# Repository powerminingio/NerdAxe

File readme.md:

# The Nerdaxe
NerdAxe is a fork from bitaxe with fullcolor display graphics. NerdAxe is indented to be an upgrade board for these who have a NerdMiner and would like to have more powerful mining features without losing the NerdMiner essence. That's why NerdAxe is currently controlled by the common board used on Nerdminer project called TTGO-TDisplayS3.

Currently exists two variants sepparated in two branches:
- **Nerdaxe Gamma**: 1,2Th with a single chip BM1370. [Nerdaxe Gamma](https://github.com/BitMaker-hub/NerdAxe/tree/gamma-1%2C2Ths)
- **Nerdaxe Ultra**: 0,5Th with a single chip BM1366. [Nerdaxe Ultra](https://github.com/BitMaker-hub/NerdAxe/tree/ultra-500Ghs)

The following fork could not be possible without the previous work of @skot, @ben & bitaxe devs. [Check bitaxe project](https://bitaxe.org)

Upgrade your NerdMiner experience throught this addon board and start playing with ASICs

## Goals
- **Plug&Play**: your NerdMiner board and convert it into a NerdAxe.
- **Standalone**: can mine directly to your pool over WiFi. No External computer needed.
- **Embedded**: low cost, low maintenance, high availability, high reliability, low power.
- **ASIC**: working with most efficient ASIC chips from Bitmain - BM1370.
- **Versatile**: solo/pool mining, autotune power/heat/efficiency.
- **Open Source**: All design files are provided.

## Features
- **TTGO-TDisplay** ESP32s3 wifi microcontroller display board
- **Multiple Screens** to allow you see all the miner stats 
- **TI TPS546D** buck regulator steps down the 5V input to power the BM1370
- **Microchip EMC2101** PWM controls the fan and monitors tach output. Measuring internal die temp isn't working.

## Additional Features added by Powermining
- **Two fan connectors** - no need for splitter cable if you use secondary fan.
- **Threaded heatsink mounting holes** PCB with M3 threads for firm heatsink mounting
- **OG matching heatsink bolt pattern** no headache with non fitting standard bolt patterns! We keep the Nerdaxe standard 41.49x41.35

## Software & Firmware
Nerdaxe firmware was forked from original ESP-Miner version and adapted to use TTGO board and LVGL as graphic interface lib. 
Check it here -> [ESP-Miner Nerdaxe version](https://github.com/BitMaker-hub/ESP-Miner-NerdAxe)

**Today** Nerdaxe is using the latest evolution of this firmware modified by @pmaxuw (creator of the NerdQaxe) and used for other multiple boards
Current firmware -> [ESP-Miner Nerd\*axe version](https://github.com/shufps/ESP-Miner-NerdQAxePlus)

Flash the latest Nerdaxe firmware here: 
- Go to flasher online tool: https://flasher.bitronics.store/ (recommend via Google Chrome incognito mode)
- Nerd\*axe flasher online tool: https://shufps.github.io/nerdqaxe-web-flasher/  

## The DIY area

### Asic BM1370
- The BM1370 is a undocumented SHA256 mining ASIC from Bitmain. It's mostly used in the Antminer S21pro/S21+
- Bitmain claims the BM1370 has 0.021J/GH efficiency
- The BM1370 is available (new) for around $60 each in small quantities.
- The BM1370 has a different footprint and pinout from the MB1366, BM1368 in previous bitaxe.

### Other components & build troubleshooting
- BM1370 from NBTC on AliExpress
- [40x40mm heatsink and 5V fan](https://www.aliexpress.com/item/2251832861666365.html) from a random AliExpress seller. At least half of these arrived broken in some way. But they are cheap and the working ones do keep the BM1387's nice and cool when used with some thermal compound.
    - Swap this fan with the [Noctua NF-A4x10](https://noctua.at/en/products/fan/nf-a4x10-pwm) 5V 4-Pin fan for a much more pleasant experience.
- Board is designed with [KiCad 8](https://www.kicad.org) design files
- All of the parts on the board are listed in the KiCad BOM
- Check out [building.md](building.md) for PCB ordering tips
- Check out [assembly.md](assembly.md) for assembly tips

### Power Supply Requirements
- 5VDC Power supply 5A minimum. Should be capable of over 25W

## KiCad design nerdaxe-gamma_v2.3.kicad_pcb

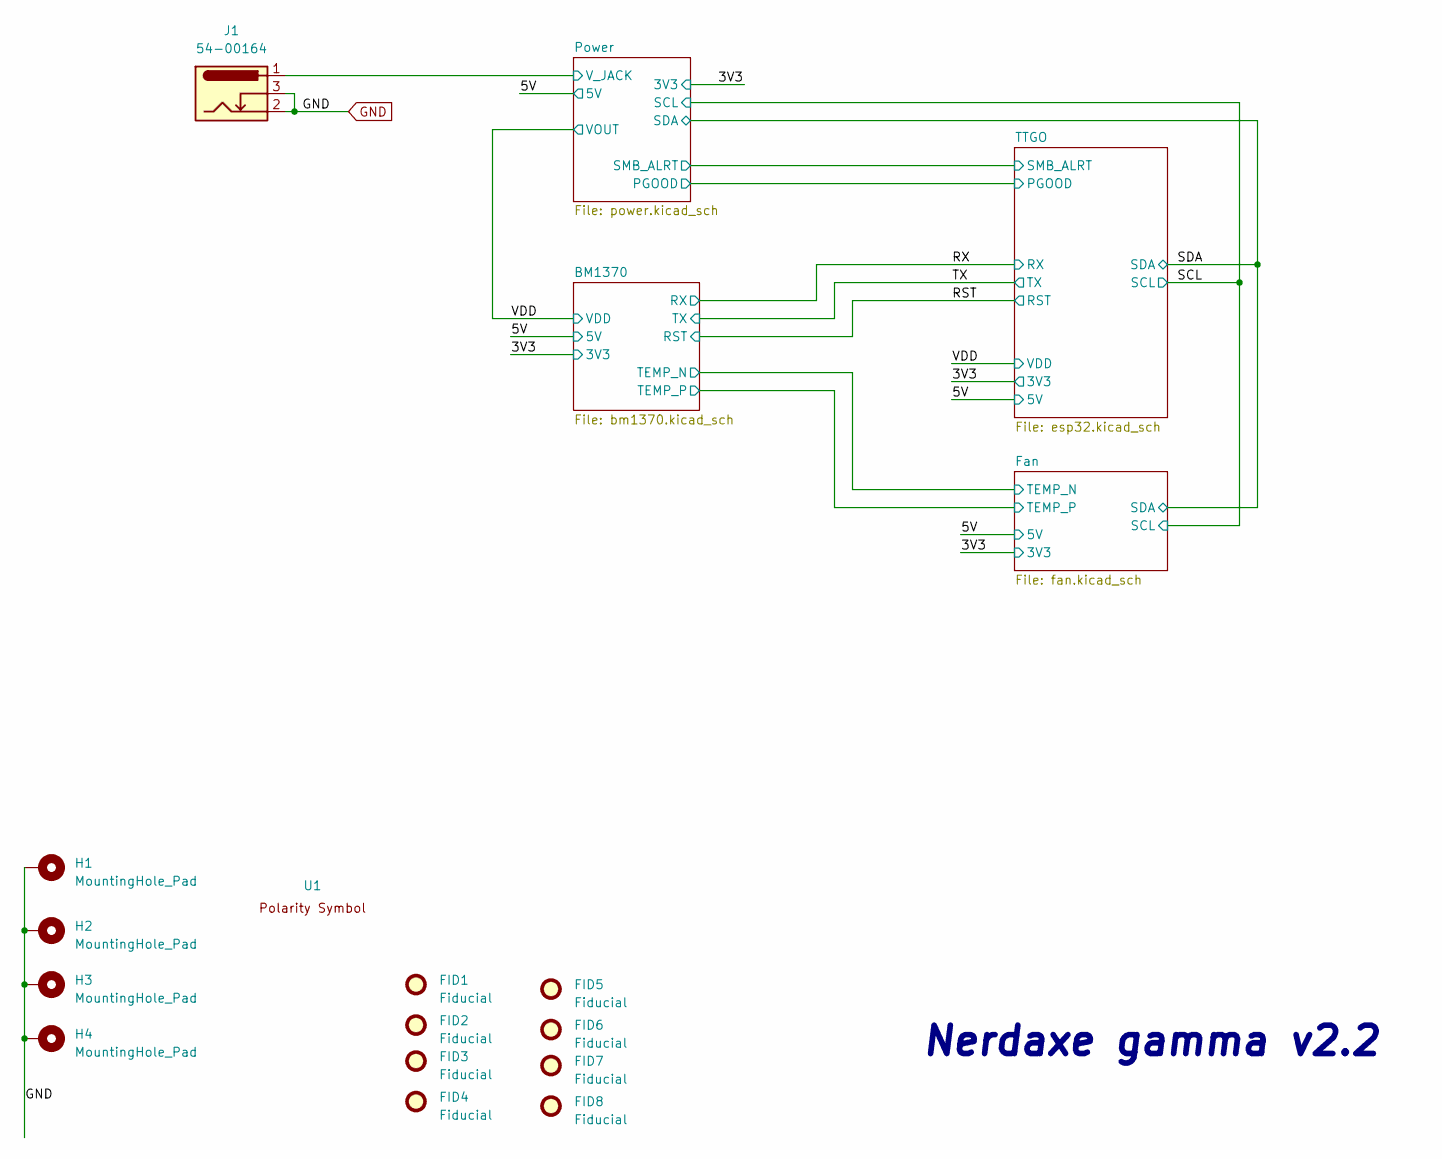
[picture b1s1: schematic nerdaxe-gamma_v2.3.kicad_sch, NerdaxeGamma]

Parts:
FID1, FID2, FID3, FID4, FID5, FID6, FID7, FID8: Fiducial; Fiducial_1mm_Mask2mm
H1, H2, H3, H4: MountingHole_Pad; MountingHole_3mm_Pad_Via
J1: 54-00164; TENSILITY_54-00164; PARTNO 54-00164; LCSC C431534
U1: polarity

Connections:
/Power/V_JACK: J1.1; also elsewhere on the board
GND: H1.1, H2.1, H3.1, H4.1, J1.2, J1.3; also elsewhere on the board

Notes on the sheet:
Nerdaxe gamma v2.2

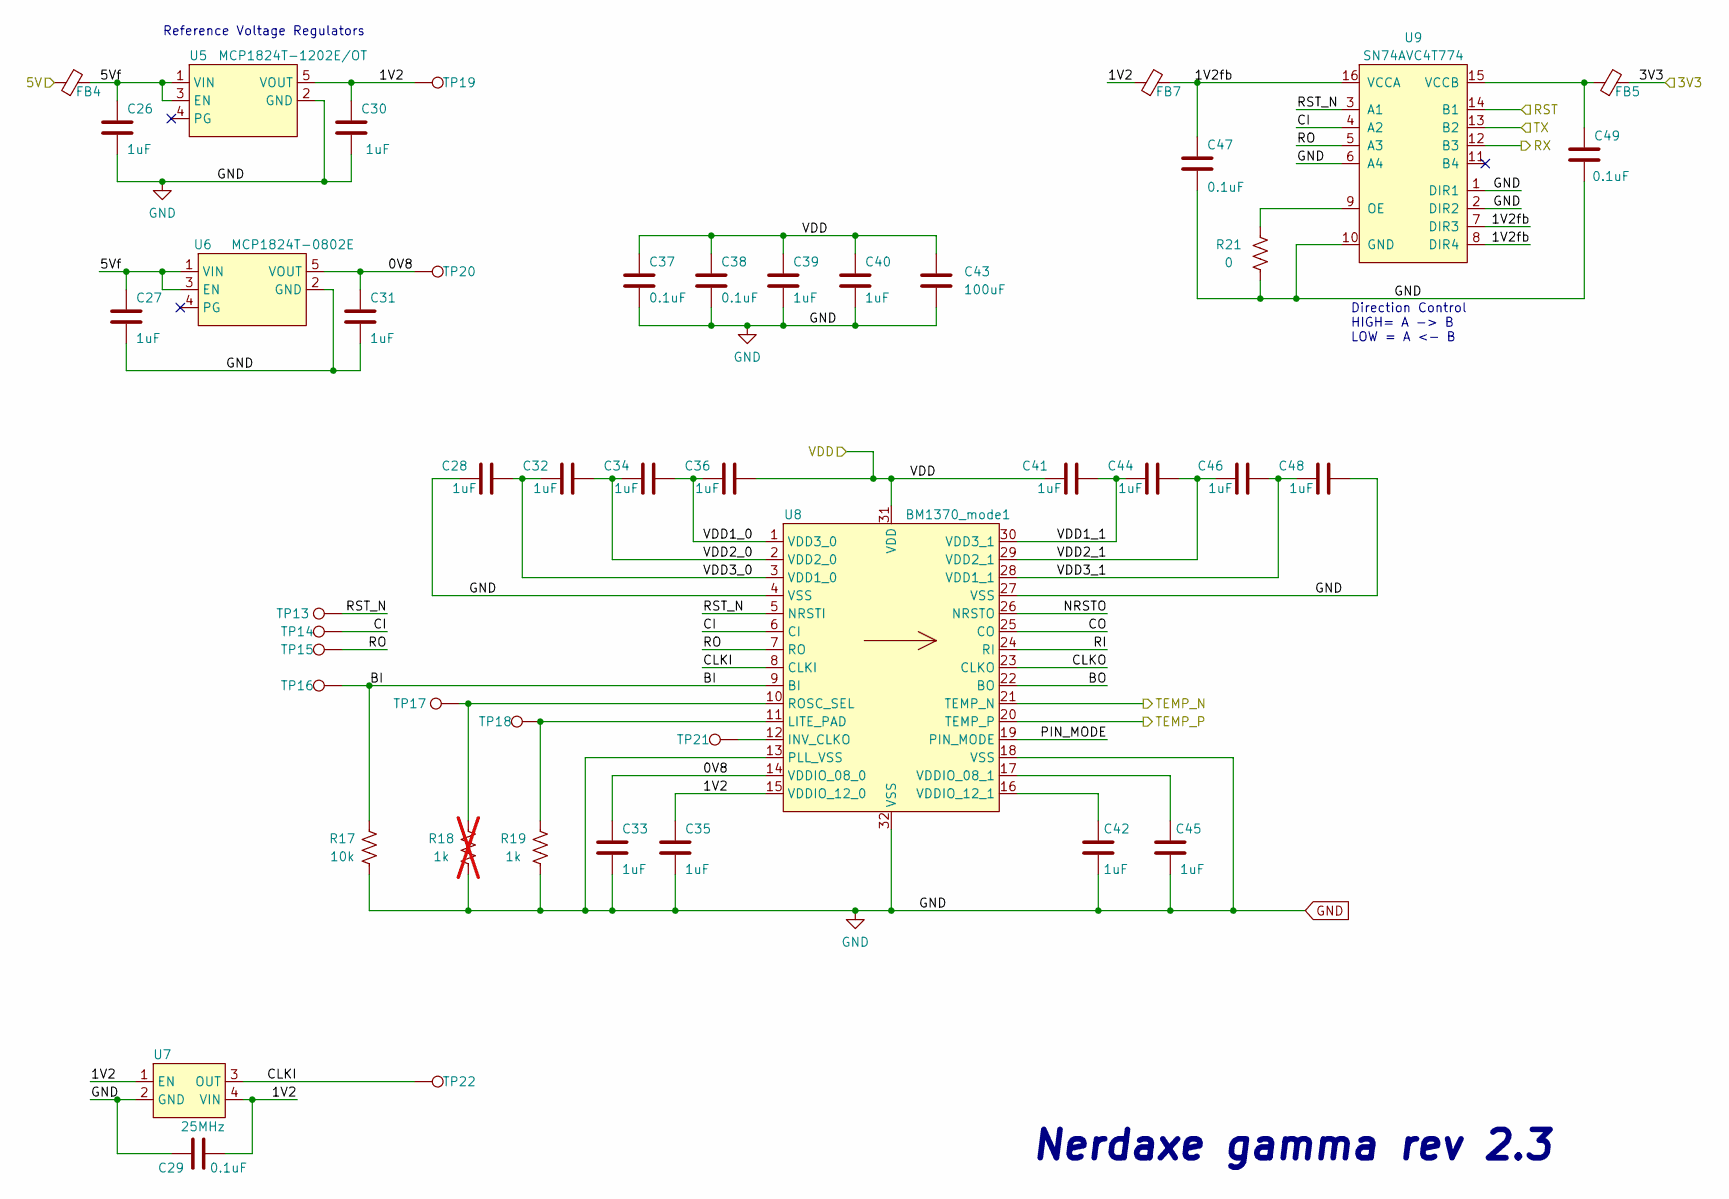
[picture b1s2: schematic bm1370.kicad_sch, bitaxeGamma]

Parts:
C26, C27, C28, C30, C31, C32, C33, C34, C35, C36, C39, C40, C41, C42, C44, C45, C46, C48: 1uF; C_0402_1005Metric; PARTNO EMK105BJ105MV-F
C29, C37, C38, C47, C49: 0.1uF; C_0402_1005Metric; PARTNO CL05A104KO5NNNC
C43: 100uF; C_1206_3216Metric; PARTNO CL31A107MQHNNNE
FB4, FB5, FB7: BLM21PG221SN1D; R_0805_2012Metric
R17: 10k; R_0402_1005Metric; PARTNO RC0402JR-0710KL
R18: 1k; R_0402_1005Metric; PARTNO RC0402FR-071KL; not fitted
R19: 1k; R_0402_1005Metric; PARTNO RC0402FR-071KL
R21: 0; R_0402_1005Metric; PARTNO RC0402FR-0720KL
TP13, TP14, TP15, TP16, TP17, TP18, TP19, TP20, TP21, TP22: TestPoint; TestPoint_Pad_D1.5mm
U5: MCP1824T-1202E/OT; SOT-23-5; PARTNO MCP1824T-1202E/OT
U6: MCP1824T-0802E; SOT-23-5; PARTNO MCP1824T-0802E/OT
U7: 25MHz; SMD3225-4P; PARTNO SX3M25.000E20F30THN; LCSC C5137262
U8: BM1370_mode1; BM1370
U9: SN74AVC4T774; TSSOP-16_4.4x5mm_P0.65mm; PARTNO SN74AVC4T774PWR

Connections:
/3V3: FB5.2; also elsewhere on the board
/5V: FB4.1; also elsewhere on the board
/BM1370/0V8: C31.1, C33.1, TP20.1, U6.5 (VOUT), U8.14 (VDDIO_08_0)
/BM1370/1V2: C29.2, C30.1, C35.1, FB7.1, TP19.1, U5.5 (VOUT), U7.1 (EN), U7.4 (VIN), U8.15 (VDDIO_12_0)
/BM1370/1V2fb: C47.1, FB7.2, U9.7 (DIR3), U9.8 (DIR4), U9.16 (VCCA)
/BM1370/5Vf: C26.1, C27.1, FB4.2, U5.1 (VIN), U5.3 (EN), U6.1 (VIN), U6.3 (EN)
/BM1370/BI: R17.2, TP16.1, U8.9 (BI)
/BM1370/BO: U8.22 (BO)
/BM1370/CI: TP14.1, U8.6 (CI), U9.4 (A2)
/BM1370/CLKI: TP22.1, U7.3 (OUT), U8.8 (CLKI)
/BM1370/CLKO: U8.23 (CLKO)
/BM1370/CO: U8.25 (CO)
/BM1370/NRSTO: U8.26 (NRSTO)
/BM1370/PIN_MODE: U8.19 (PIN_MODE)
/BM1370/RI: U8.24 (RI)
/BM1370/RO: TP15.1, U8.7 (RO), U9.5 (A3)
/BM1370/RST_N: TP13.1, U8.5 (NRSTI), U9.3 (A1)
/BM1370/VDD1_0: C34.2, C36.1, U8.1 (VDD3_0)
/BM1370/VDD1_1: C41.2, C44.1, U8.30 (VDD3_1)
/BM1370/VDD2_0: C32.2, C34.1, U8.2 (VDD2_0)
/BM1370/VDD2_1: C44.2, C46.1, U8.29 (VDD2_1)
/BM1370/VDD3_0: C28.2, C32.1, U8.3 (VDD1_0)
/BM1370/VDD3_1: C46.2, C48.1, U8.28 (VDD1_1)
/Fan/TEMP_N: U8.21 (TEMP_N); also elsewhere on the board
/Fan/TEMP_P: U8.20 (TEMP_P); also elsewhere on the board
/RST: U9.14 (B1); also elsewhere on the board
/RX: U9.12 (B3); also elsewhere on the board
/TX: U9.13 (B2); also elsewhere on the board
/VDD: C36.2, C37.1, C38.1, C39.1, C40.1, C41.1, C43.1, U8.31 (VDD); also elsewhere on the board
GND: C26.2, C27.2, C28.1, C29.1, C30.2, C31.2, C33.2, C35.2, C37.2, C38.2, C39.2, C40.2, C42.2, C43.2, C45.2, C47.2, C48.2, C49.2, R17.1, R18.1, R19.1, R21.1, U5.2 (GND), U6.2 (GND), U7.2 (GND), U8.4 (VSS), U8.13 (PLL_VSS), U8.18 (VSS), U8.27 (VSS), U8.32 (VSS), U9.1 (DIR1), U9.2 (DIR2), U9.6 (A4), U9.10 (GND); also elsewhere on the board
unnamed: TP21.1, U8.12 (INV_CLKO)
unnamed: R19.2, TP18.1, U8.11 (LITE_PAD)
unnamed: R18.2, TP17.1, U8.10 (ROSC_SEL)
unnamed: C45.1, U8.17 (VDDIO_08_1)
unnamed: C42.1, U8.16 (VDDIO_12_1)
unnamed: R21.2, U9.9 (OE)
unnamed: C49.1, FB5.1, U9.15 (VCCB)

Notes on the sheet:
Reference Voltage Regulators
Direction Control HIGH= A -> B LOW = A <- B
Nerdaxe gamma rev 2.3

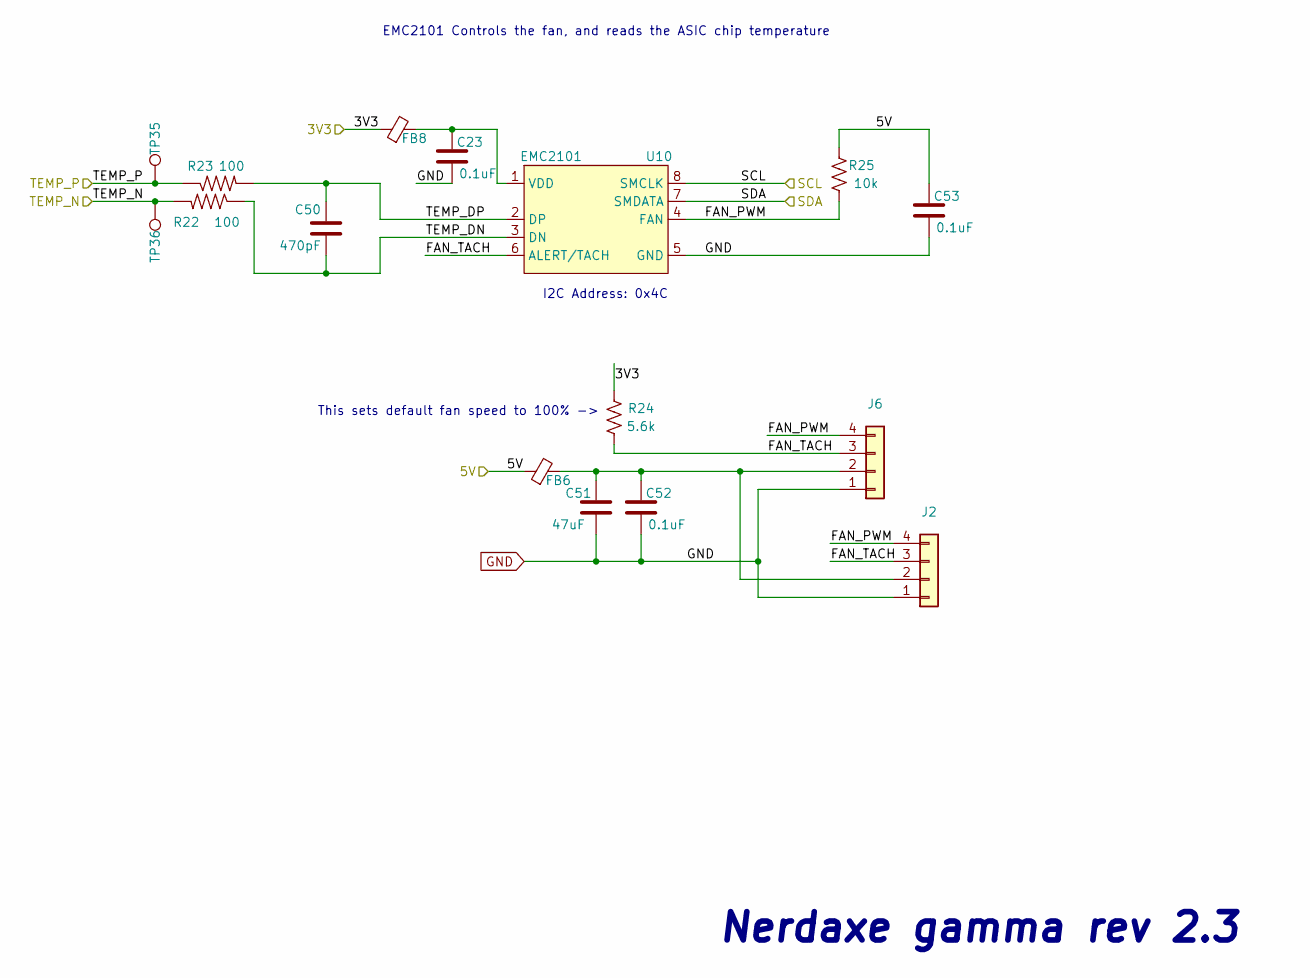
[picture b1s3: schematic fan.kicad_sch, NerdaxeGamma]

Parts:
C23, C52, C53: 0.1uF; C_0402_1005Metric; PARTNO CL05A104KO5NNNC
C50: 470pF; C_0402_1005Metric; PARTNO CL05B471KB5NNNC
C51: 47uF; C_1210_3225Metric; PARTNO CL32A476KOJNNNE
FB6, FB8: BLM21PG221SN1D; R_0805_2012Metric
J2, J6: Conn_01x04; 470531000; PARTNO 0470531000
R22, R23: 100; R_0402_1005Metric; PARTNO RC0402FR-07100RL
R24: 5.6k; R_0402_1005Metric; PARTNO RC0402FR-135K6L
R25: 10k; R_0402_1005Metric; PARTNO RC0402JR-0710KL
TP35, TP36: TestPoint; TestPoint_Pad_D1.5mm
U10: EMC2101; TSSOP-8_3x3mm_P0.65mm; PARTNO EMC2101-R-ACZL-TR

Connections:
/3V3: FB8.1, R24.2; also elsewhere on the board
/5V: C53.1, FB6.1, R25.2; also elsewhere on the board
/Fan/FAN_PWM: J2.4, J6.4, R25.1, U10.4 (FAN)
/Fan/FAN_TACH: J2.3, J6.3, R24.1, U10.6 (ALERT/TACH)
/Fan/TEMP_DN: C50.2, R22.1, U10.3 (DN)
/Fan/TEMP_DP: C50.1, R23.2, U10.2 (DP)
/Fan/TEMP_N: R22.2, TP36.1; also elsewhere on the board
/Fan/TEMP_P: R23.1, TP35.1; also elsewhere on the board
/SCL: U10.8 (SMCLK); also elsewhere on the board
/SDA: U10.7 (SMDATA); also elsewhere on the board
GND: C23.2, C51.2, C52.2, C53.2, J2.1, J6.1, U10.5 (GND); also elsewhere on the board
unnamed: C51.1, C52.1, FB6.2, J2.2, J6.2
unnamed: C23.1, FB8.2, U10.1 (VDD)

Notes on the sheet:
Nerdaxe gamma rev 2.3
EMC2101 Controls the fan, and reads the ASIC chip temperature
This sets default fan speed to 100% ->
I2C Address: 0x4C

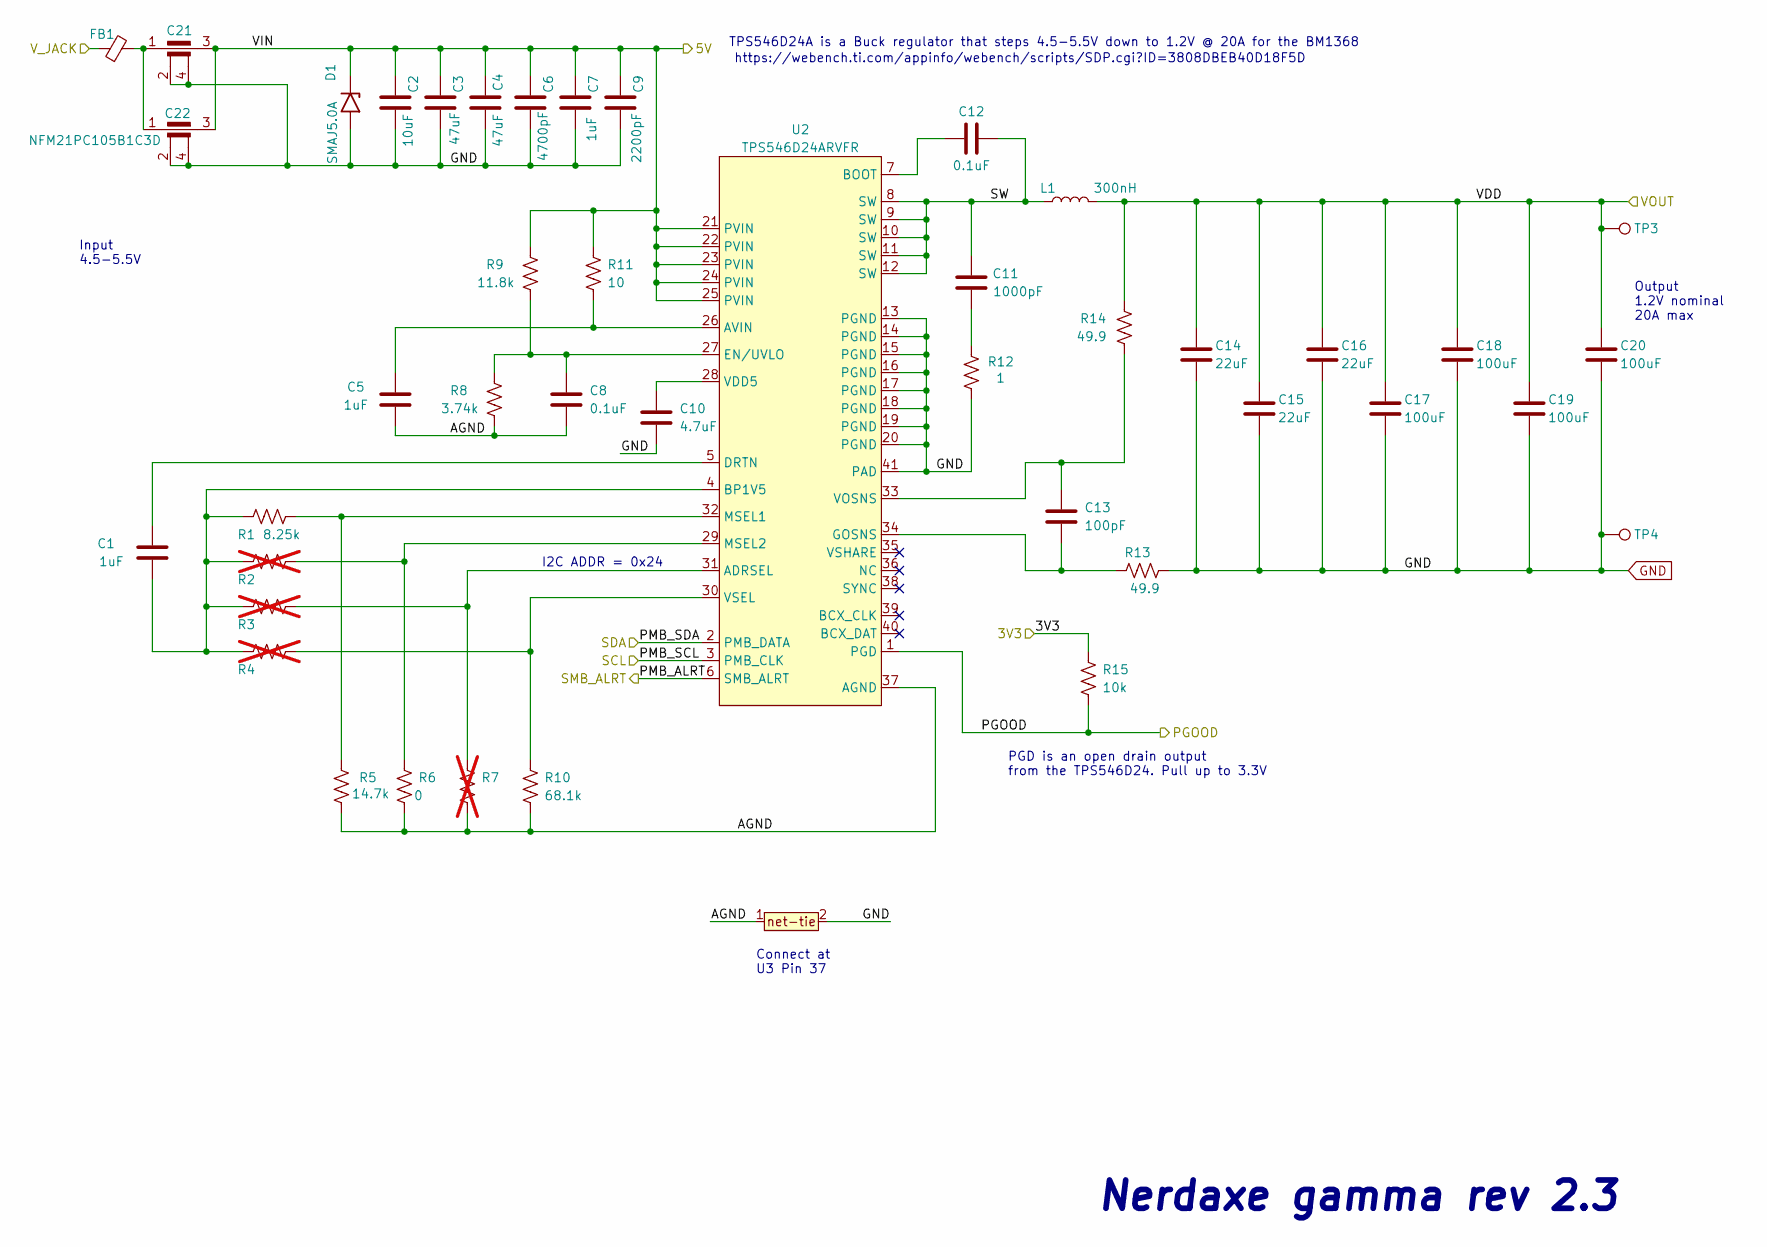
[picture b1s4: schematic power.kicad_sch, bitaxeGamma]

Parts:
C1, C5, C7: 1uF; C_0402_1005Metric; PARTNO EMK105BJ105MV-F
C2: 10uF; C_0805_2012Metric; PARTNO CL21A106KOQNNNE
C3, C4: 47uF; C_1210_3225Metric; PARTNO CL32A476KOJNNNE
C6: 4700pF; C_0402_1005Metric; PARTNO GRM155R71E472KA01D
C8, C12: 0.1uF; C_0402_1005Metric; PARTNO CL05A104KO5NNNC
C9: 2200pF; C_0402_1005Metric; PARTNO GRM155R61H222KA01D
C10: 4.7uF; C_0402_1005Metric; PARTNO GRM155R61A475MEAAD
C11: 1000pF; C_0805_2012Metric; PARTNO CC0805KRX7R9BB102
C13: 100pF; C_0402_1005Metric; PARTNO 885012005013
C14, C15, C16: 22uF; C_0805_2012Metric; PARTNO GRM21BR61A226ME44L
C17, C18, C19, C20: 100uF; C_1206_3216Metric; PARTNO CL31A107MQHNNNE
C21, C22: NFM21PC105B1C3D; NFM21PC105B1C3D_MUR
D1: SMAJ5.0A; D_SMA
FB1: 2508051217Y6; R_0805_2012Metric
L1: 300nH; SLC1175-271MEC_COC; PARTNO SLC1175-301MEC; Mouser 994-SLC1175-271MEC
R1: 8.25k; R_0402_1005Metric; PARTNO RC0402FR-078K25L
R2, R3, R4, R7: R_0402_1005Metric; not fitted
R5: 14.7k; R_0402_1005Metric; PARTNO RC0402FR-0714K7L
R6: 0; R_0402_1005Metric; PARTNO RC0402JR-070RL
R8: 3.74k; R_0402_1005Metric; PARTNO RC0402FR-073K74L
R9: 11.8k; R_0402_1005Metric; PARTNO RC0402FR-0711K8L
R10: 68.1k; R_0402_1005Metric; PARTNO RC0402FR-0768K1L
R11: 10; R_0402_1005Metric; PARTNO RC0402FR-0710RL
R12: 1; R_1206_3216Metric; PARTNO CSR1206FT1R00
R13, R14: 49.9; R_0402_1005Metric; PARTNO RC0402FR-0749R9L
R15: 10k; R_0402_1005Metric; PARTNO RC0402JR-0710KL
T1: net-tie; NetTie-0.25mm
TP3, TP4: TestPoint; TestPoint_Pad_D1.5mm
U2: TPS546D24ARVFR; LQFN40-CLIP; PARTNO TPS546D24ARVFR

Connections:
/3V3: R15.2; also elsewhere on the board
/5V: C2.1, C3.1, C4.1, C6.1, C7.1, C9.1, C21.3, C22.3, D1.1 (A1), R9.1, R11.1, U2.21 (PVIN), U2.22 (PVIN), U2.23 (PVIN), U2.24 (PVIN), U2.25 (PVIN); also elsewhere on the board
/Power/AGND: C5.1, C8.2, R5.1, R6.2, R7.2, R8.2, R10.2, T1.1, U2.37 (AGND)
/Power/PGOOD: R15.1, U2.1 (PGD); also elsewhere on the board
/Power/PMB_ALRT: U2.6 (SMB_ALRT); also elsewhere on the board
/Power/SW: C11.2, C12.2, L1.1, U2.8 (SW), U2.9 (SW), U2.10 (SW), U2.11 (SW), U2.12 (SW)
/Power/V_JACK: FB1.1; also elsewhere on the board
/SCL: U2.3 (PMB_CLK); also elsewhere on the board
/SDA: U2.2 (PMB_DATA); also elsewhere on the board
/VDD: C14.1, C15.1, C16.1, C17.1, C18.1, C19.1, C20.1, L1.2, R14.1, TP3.1; also elsewhere on the board
GND: C2.2, C3.2, C4.2, C6.2, C7.2, C9.2, C10.2, C14.2, C15.2, C16.2, C17.2, C18.2, C19.2, C20.2, C21.2, C21.4, C22.2, C22.4, D1.2 (A2), R12.1, R13.2, T1.2, TP4.1, U2.13 (PGND), U2.14 (PGND), U2.15 (PGND), U2.16 (PGND), U2.17 (PGND), U2.18 (PGND), U2.19 (PGND), U2.20 (PGND), U2.41 (PAD); also elsewhere on the board
unnamed: C11.1, R12.2
unnamed: C21.1, C22.1, FB1.2
unnamed: R3.2, R7.1, U2.31 (ADRSEL)
unnamed: C5.2, R11.2, U2.26 (AVIN)
unnamed: C12.1, U2.7 (BOOT)
unnamed: C1.2, R1.1, R2.1, R3.1, R4.1, U2.4 (BP1V5)
unnamed: C1.1, U2.5 (DRTN)
unnamed: C8.1, R8.1, R9.2, U2.27 (EN/UVLO)
unnamed: C13.2, R13.1, U2.34 (GOSNS)
unnamed: R1.2, R5.2, U2.32 (MSEL1)
unnamed: R2.2, R6.1, U2.29 (MSEL2)
unnamed: C10.1, U2.28 (VDD5)
unnamed: C13.1, R14.2, U2.33 (VOSNS)
unnamed: R4.2, R10.1, U2.30 (VSEL)

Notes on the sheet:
TPS546D24A is a Buck regulator that steps 4.5-5.5V down to 1.2V @ 20A for the BM1368
https://webench.ti.com/appinfo/webench/scripts/SDP.cgi?ID=3808DBEB40D18F5D
Input 4.5-5.5V
Nerdaxe gamma rev 2.3
PGD is an open drain output from the TPS546D24. Pull up to 3.3V
I2C ADDR = 0x24
Output 1.2V nominal 20A max
Connect at U3 Pin 37

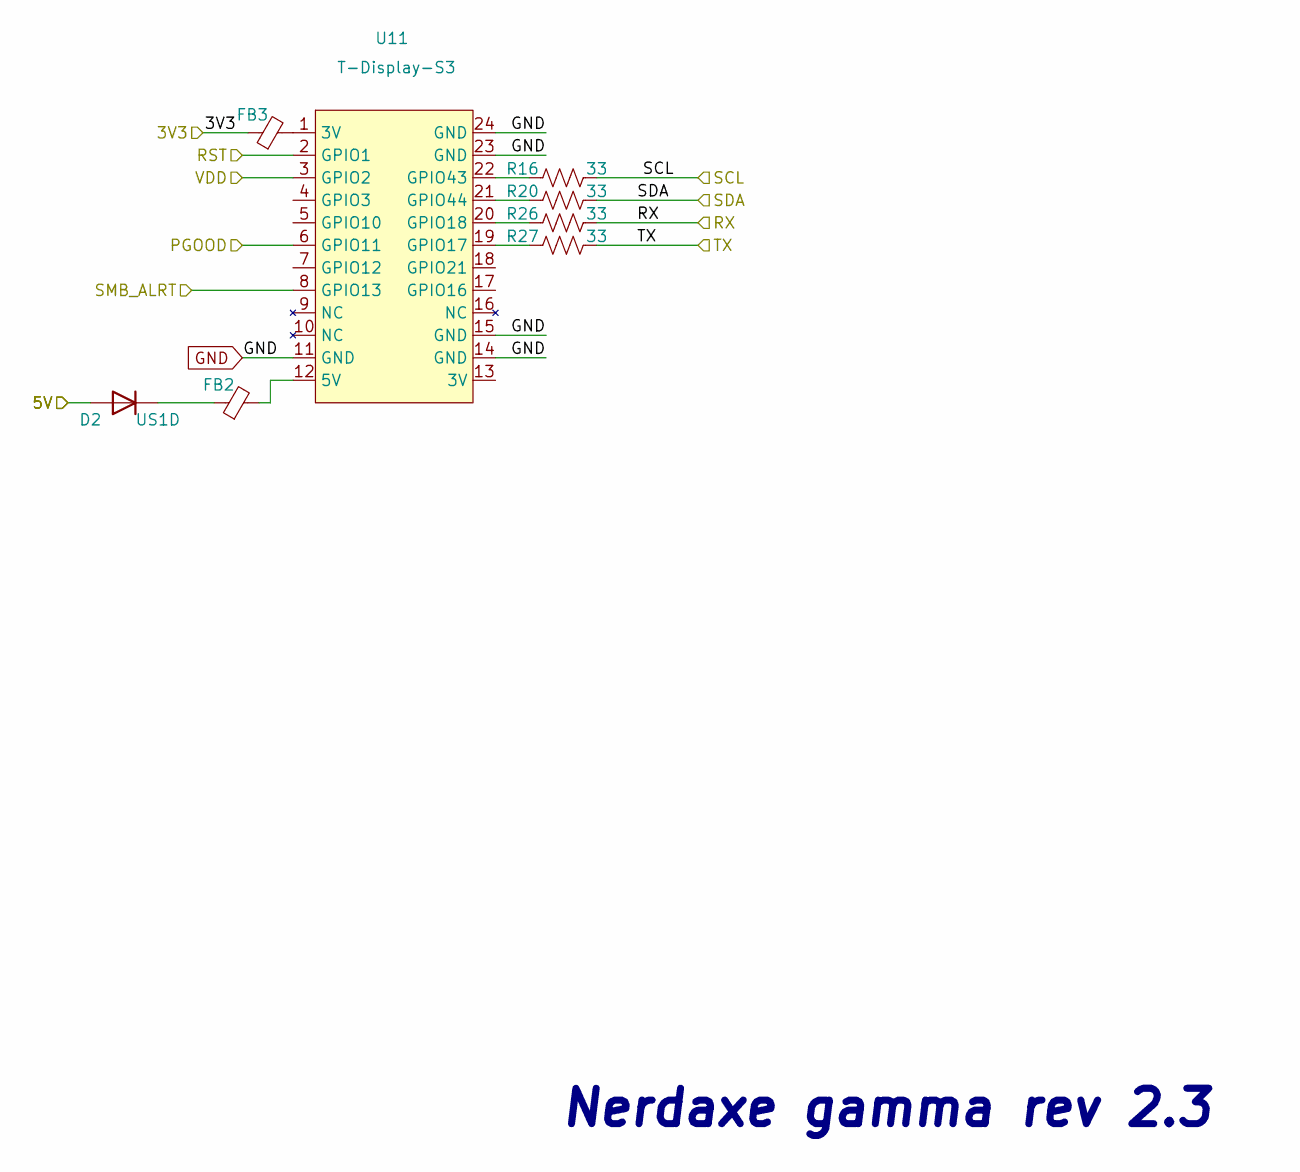
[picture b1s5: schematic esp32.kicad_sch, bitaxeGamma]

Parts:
D2: US1D; D_SMA
FB2: MPZ2012S221A; R_0805_2012Metric
FB3: BLM21PG221SN1D; R_0805_2012Metric
R16, R20, R26, R27: 33; R_0805_2012Metric; PARTNO RC0402FR-0710RL
U11: T-Display-S3

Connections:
/3V3: FB3.1; also elsewhere on the board
/5V: D2.2 (A); also elsewhere on the board
/Power/PGOOD: U11.6 (GPIO11); also elsewhere on the board
/Power/PMB_ALRT: U11.8 (GPIO13); also elsewhere on the board
/RST: U11.2 (GPIO1); also elsewhere on the board
/RX: R26.2; also elsewhere on the board
/SCL: R16.2; also elsewhere on the board
/SDA: R20.2; also elsewhere on the board
/TX: R27.2; also elsewhere on the board
/VDD: U11.3 (GPIO2); also elsewhere on the board
GND: U11.11 (GND), U11.14 (GND), U11.15 (GND), U11.23 (GND), U11.24 (GND); also elsewhere on the board
unnamed: D2.1 (K), FB2.1
unnamed: FB3.2, U11.1 (3V)
unnamed: FB2.2, U11.12 (5V)
unnamed: R27.1, U11.19 (GPIO17)
unnamed: R26.1, U11.20 (GPIO18)
unnamed: R16.1, U11.22 (GPIO43)
unnamed: R20.1, U11.21 (GPIO44)

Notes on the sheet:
Nerdaxe gamma rev 2.3

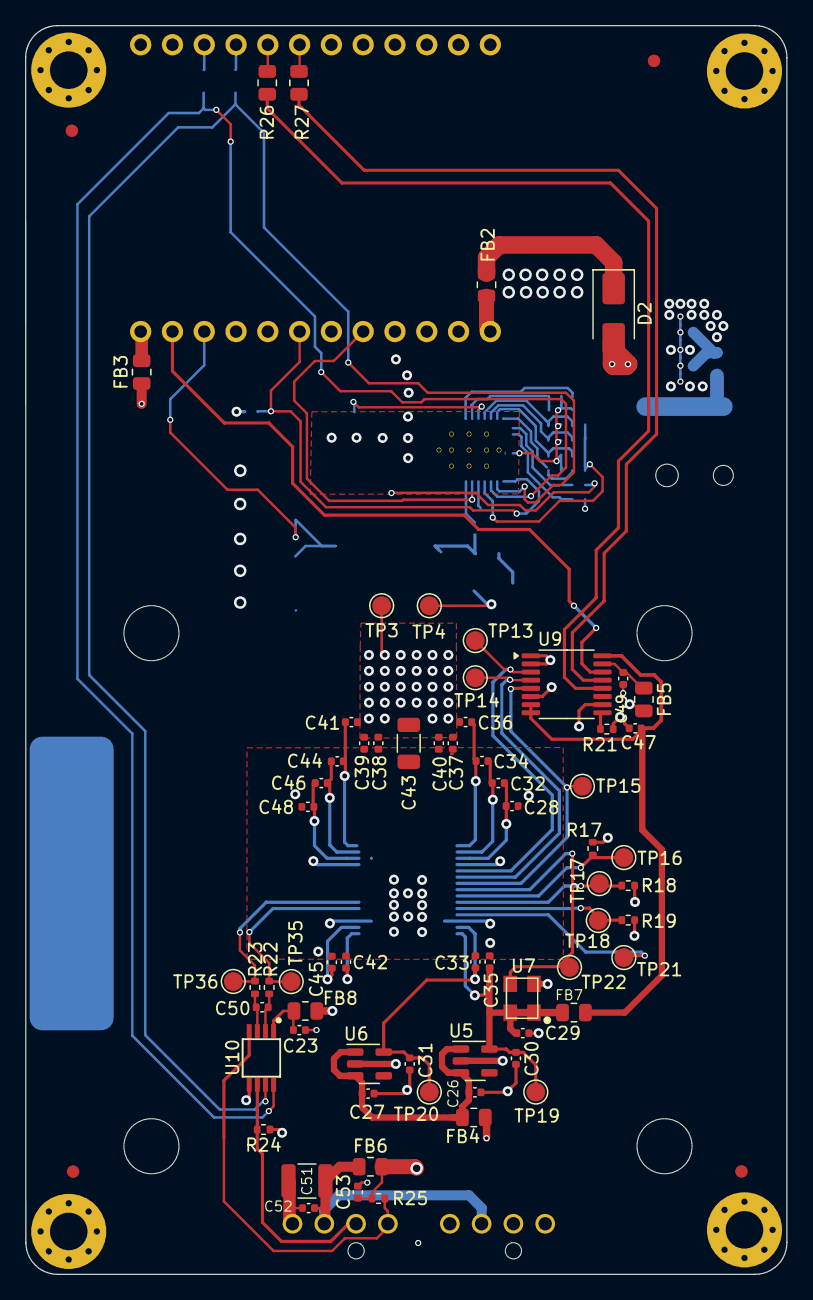
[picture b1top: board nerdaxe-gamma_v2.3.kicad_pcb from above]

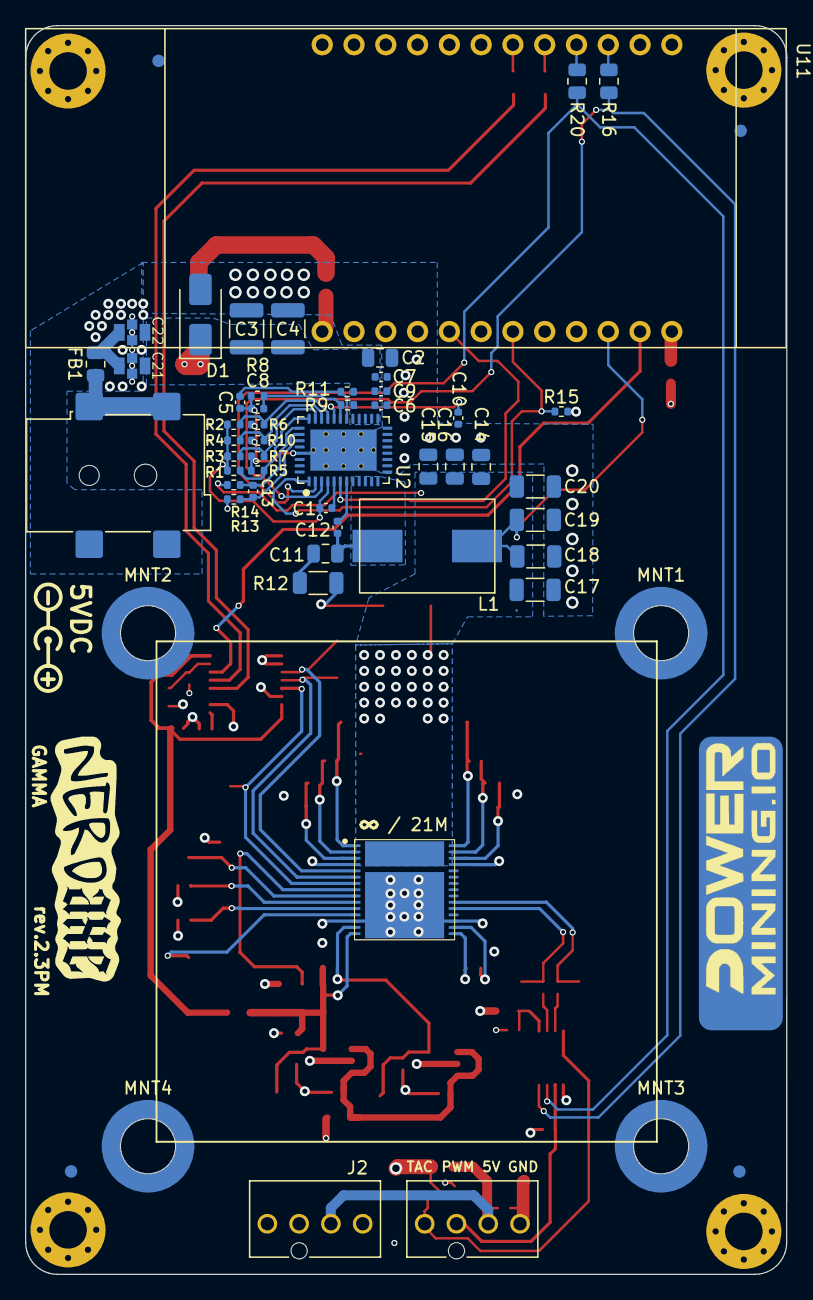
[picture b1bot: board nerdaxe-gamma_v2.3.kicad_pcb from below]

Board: 4 copper layers, 60.8 x 99.8 mm, 132 parts (58 on the bottom side), 65 nets.

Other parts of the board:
MNT1, MNT2, MNT3, MNT4: Mounting_Wuerth_WA-SMSI-M3_H0.5mm_9774005360

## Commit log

2025-12-10 Powermining upgrades
2025-12-12 Corrected device name in readme
